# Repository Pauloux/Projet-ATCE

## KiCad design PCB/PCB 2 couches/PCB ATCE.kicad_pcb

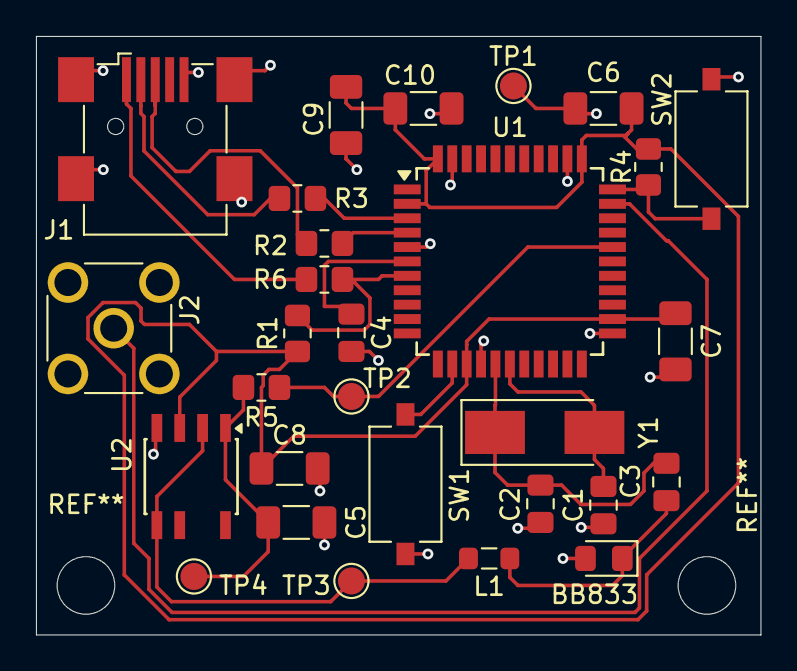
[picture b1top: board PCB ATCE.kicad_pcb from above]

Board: 2 copper layers, 40.2 x 33.2 mm, 29 parts (0 on the bottom side), 18 nets.

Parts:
BB833: D_0805_2012Metric_Pad1.15x1.40mm_HandSolder
C1: 15p; C_0805_2012Metric_Pad1.18x1.45mm_HandSolder
C2: 10p; C_0805_2012Metric_Pad1.18x1.45mm_HandSolder
C3, C4: 1u; C_0805_2012Metric_Pad1.18x1.45mm_HandSolder
C5, C6, C7, C8, C9, C10: 10u; C_1206_3216Metric_Pad1.33x1.80mm_HandSolder
J1: USB_OTG; USB_Mini-B_Wuerth_65100516121_Horizontal
J2: Conn_Coaxial; SMA_Molex_73251-2200_Horizontal
L1: 10u; L_0805_2012Metric_Pad1.05x1.20mm_HandSolder
R1, R6: 0; R_0805_2012Metric_Pad1.20x1.40mm_HandSolder
R2, R3: 22; R_0805_2012Metric_Pad1.20x1.40mm_HandSolder
R4, R5: 5k; R_0805_2012Metric_Pad1.20x1.40mm_HandSolder
SW1, SW2: SW_Push; SW_Tactile_SPST_NO_Straight_CK_PTS636Sx25SMTRLFS
TP1, TP2, TP3, TP4: TestPoint; TestPoint_Pad_D1.5mm
U1: TQFP-44_10x10mm_P0.8mm
U2: SOIC-8-N7_3.9x4.9mm_P1.27mm
Y1: 16MHz; Crystal_SMD_Abracon_ABM3-2Pin_5.0x3.2mm_HandSoldering

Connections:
+5V: C6.1, C7.1, C8.1, C9.1, C10.1, R1.1, R4.1, U1.2 (UVCC), U1.14 (VCC), U1.24 (AVCC), U1.34 (VCC), U1.44 (AVCC), U2.3 (V+)
/D1+: R2.2, U1.4 (D+)
/D1-: R3.2, U1.3 (D-)
/D+: J1.3 (D+), R2.1
/D-: J1.2 (D-), R3.1
GND: BB833.2 (A), C1.1, C2.1, C4.2, C5.2, C6.2, C7.2, C8.2, C9.2, C10.2, J1.5 (GND), J1.6 (Shield), J2.2 (Ext), SW1.1, SW2.2, TP1.1, U1.5 (UGND), U1.15 (GND), U1.23 (GND), U1.35 (GND), U1.43 (GND), U2.4 (V-)
unnamed: BB833.1 (K), C3.2, L1.1
unnamed: J1.1 (VBUS), R6.1
unnamed: J2.1 (In), U1.32 ((ICP3/CLK0/OC4A)PC7)
unnamed: R5.1, TP2.1, U1.29 ((ADC12/OC1A/~OC4B/PCINT5)PB5)
unnamed: R4.2, SW2.1, U1.33 ((~HWB)PE2)
unnamed: C4.1, U1.6 (UCAP)
unnamed: R1.2, R6.2, U1.7 (VBUS)
unnamed: C1.2, U1.17 (XTAL1), Y1.2
unnamed: C2.2, C3.1, U1.16 (XTAL2), Y1.1
unnamed: SW1.2, U1.13 (~RESET)
unnamed: C5.1, R5.2, TP4.1, U2.1 (+)
unnamed: L1.2, TP3.1, U2.2 (-), U2.5

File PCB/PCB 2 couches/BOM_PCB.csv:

"Reference","Value","Datasheet","Footprint","Qty","Prix/U"
"BB833","~","https://www.farnell.com/datasheets/1835977.pdf","Diode_SMD:D_0805_2012Metric_Pad1.15x1.40mm_HandSolder","1","0,172 €"
"C1","15p","https://www.yageo.com/en/Chart/Download/pdf/AC0805JRNPO9BN150","Capacitor_SMD:C_0805_2012Metric_Pad1.18x1.45mm_HandSolder","1","0,0742 €"
"C2","10p","https://www.yageo.com/en/Chart/Download/pdf/AC0805JRNPO0BN100","Capacitor_SMD:C_0805_2012Metric_Pad1.18x1.45mm_HandSolder","1","0,067 €"
"C3","1u","https://4donline.ihs.com/images/VipMasterIC/IC/YAGO/YAGO-S-A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","Capacitor_SMD:C_0805_2012Metric_Pad1.18x1.45mm_HandSolder","1","0,0982 €"
"C4","1u","https://4donline.ihs.com/images/VipMasterIC/IC/YAGO/YAGO-S-A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","Capacitor_SMD:C_0805_2012Metric_Pad1.18x1.45mm_HandSolder","1","0,0982 €"
"C5","10u","https://search.kemet.com/component-documentation/download/sp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","Capacitor_SMD:C_1206_3216Metric_Pad1.33x1.80mm_HandSolder","1","1,230 €"
"C6","10u","https://search.kemet.com/component-documentation/download/sp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","Capacitor_SMD:C_1206_3216Metric_Pad1.33x1.80mm_HandSolder","1","1,230 €"
"C7","10u","https://search.kemet.com/component-documentation/download/sp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","Capacitor_SMD:C_1206_3216Metric_Pad1.33x1.80mm_HandSolder","1","1,230 €"
"C8","10u","https://search.kemet.com/component-documentation/download/sp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","Capacitor_SMD:C_1206_3216Metric_Pad1.33x1.80mm_HandSolder","1","1,230 €"
"C9","10u","https://search.kemet.com/component-documentation/download/sp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","Capacitor_SMD:C_1206_3216Metric_Pad1.33x1.80mm_HandSolder","1","1,230 €"
"C10","10u","https://search.kemet.com/component-documentation/download/sp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","Capacitor_SMD:C_1206_3216Metric_Pad1.33x1.80mm_HandSolder","1","1,230 €"
"J1","USB_OTG","https://www.farnell.com/datasheets/2697485.pdf","Connector_USB:USB_Mini-B_Wuerth_65100516121_Horizontal","1","1,000 €"
"J2","Conn_Coaxial","https://4donline.ihs.com/images/VipMasterIC/IC/AMPH/AMPHS064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","Connector_Coaxial:SMA_Molex_73251-2200_Horizontal","1","6,940 €"
"L1","10u","http://www.farnell.com/datasheets/3006832.pdf","Inductor_SMD:L_0805_2012Metric_Pad1.05x1.20mm_HandSolder","1","0,214 €"
"R1","0","https://4donline.ihs.com/images/VipMasterIC/IC/SCMP/SCMPS001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","Resistor_SMD:R_0805_2012Metric_Pad1.20x1.40mm_HandSolder","1","0,015 €"
"R2","22","https://www.yageo.com/upload/media/product/app/datasheet/rch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","Resistor_SMD:R_0805_2012Metric_Pad1.20x1.40mm_HandSolder","1","0,016 €"
"R3","22","https://www.yageo.com/upload/media/product/app/datasheet/rch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","Resistor_SMD:R_0805_2012Metric_Pad1.20x1.40mm_HandSolder","1","0,016 €"
"R4","5k","https://www.farnell.com/datasheets/3937397.pdf","Resistor_SMD:R_0805_2012Metric_Pad1.20x1.40mm_HandSolder","1","0,015 €"
"R5","5k","https://www.farnell.com/datasheets/3937397.pdf","Resistor_SMD:R_0805_2012Metric_Pad1.20x1.40mm_HandSolder","1","0,015€"
"SW1","SW_Push","https://www.farnell.com/datasheets/3148632.pdf","Button_Switch_SMD:SW_Tactile_SPST_NO_Straight_CK_PTS636Sx25SMTRLFS","1","0,937 €"
"SW2","SW_Push","https://www.farnell.com/datasheets/3148632.pdf","Button_Switch_SMD:SW_Tactile_SPST_NO_Straight_CK_PTS636Sx25SMTRLFS","1","0,937 €"
"TP1","TestPoint","~","TestPoint:TestPoint_Keystone_5000-5004_Miniature","1",""
"TP2","TestPoint","~","TestPoint:TestPoint_Keystone_5000-5004_Miniature","1",""
"TP3","TestPoint","~","TestPoint:TestPoint_Keystone_5000-5004_Miniature","1",""
"TP4","TestPoint","~","TestPoint:TestPoint_Keystone_5000-5004_Miniature","1",""
"U1","~","https://ww1.microchip.com/downloads/en/DeviceDoc/Atmel-7766-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","Package_QFP:TQFP-44_10x10mm_P0.8mm","1","5,250 €"
"U2","","https://www.farnell.com/datasheets/630314.pdf","Package_SO:SOIC-8-N7_3.9x4.9mm_P1.27mm","1","0,353 €"
"Y1","16MHz","https://www.farnell.com/datasheets/3153929.pdf","Crystal:Crystal_SMD_Abracon_ABM3-2Pin_5.0x3.2mm_HandSoldering","1","0,258 €"

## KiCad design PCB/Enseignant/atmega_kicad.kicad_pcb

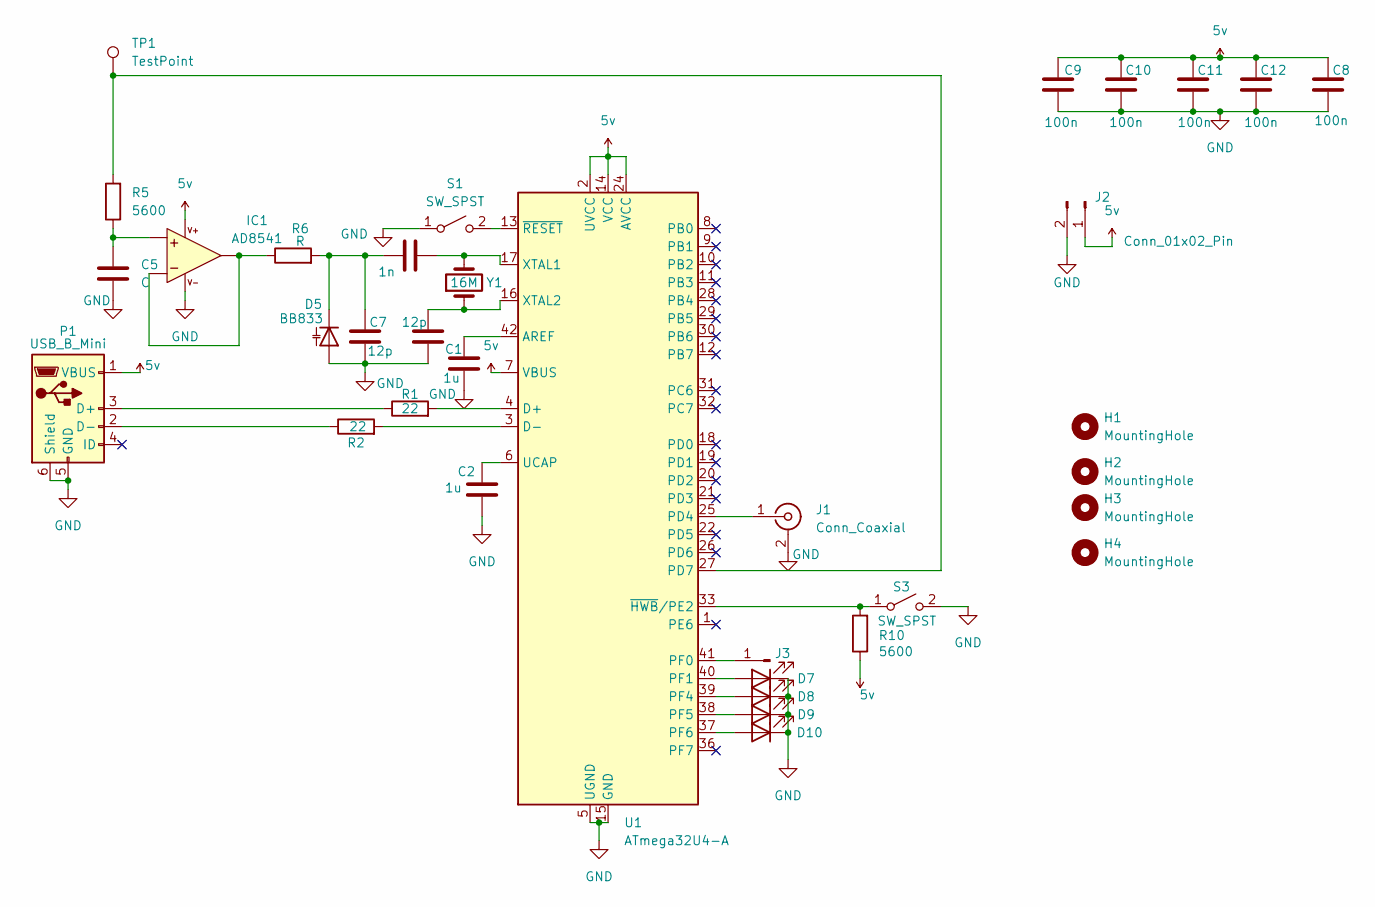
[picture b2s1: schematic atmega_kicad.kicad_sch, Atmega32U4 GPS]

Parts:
C1, C2: 1u; C_0805_2012Metric_Pad1.18x1.45mm_HandSolder
C3: 1n; C_0805_2012Metric_Pad1.18x1.45mm_HandSolder
C4, C7: 12p; C_0805_2012Metric_Pad1.18x1.45mm_HandSolder
C5: C; C_0805_2012Metric_Pad1.18x1.45mm_HandSolder
C8, C9, C10, C11, C12: 100n; C_0805_2012Metric_Pad1.18x1.45mm_HandSolder
D5: BB833; C_0805_2012Metric_Pad1.18x1.45mm_HandSolder
D7, D8, D9, D10: LED; LED_1206_3216Metric_Pad1.42x1.75mm_HandSolder
H1, H2, H3, H4: MountingHole; MountingHole_3mm
IC1: AD8541; SOT-353_SC-70-5; Farnell 1333254
J1: Conn_Coaxial; SMA_Amphenol_132134_Vertical
J2: Conn_01x02_Pin; PinHeader_1x02_P2.54mm_Vertical
J3: Conn_01x01_Pin; PinHeader_1x01_P2.54mm_Vertical
P1: USB_B_Mini; USB_Mini-B_Lumberg_2486_01_Horizontal
R1, R2: 22; R_0805_2012Metric_Pad1.20x1.40mm_HandSolder
R5, R10: 5600; R_0805_2012Metric_Pad1.20x1.40mm_HandSolder
R6: R; R_0805_2012Metric_Pad1.20x1.40mm_HandSolder
S1, S3: SW_SPST; SW_Tactile_SPST_Angled_PTS645Vx39-2LFS
TP1: TestPoint; TestPoint_Pad_1.0x1.0mm
U1: ATmega32U4-A; TQFP-44_10x10mm_P0.8mm
Y1: 16M; Crystal_HC49-U_Vertical

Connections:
5v: C8.2, C9.2, C10.2, C11.2, C12.2, IC1.5 (V+), J2.1, P1.1 (VBUS), R10.1, U1.2 (UVCC), U1.7 (VBUS), U1.14 (VCC), U1.24 (AVCC), U1.34 (VCC), U1.44 (AVCC)
GND: C1.2, C2.2, C4.1, C5.1, C7.2, C8.1, C9.1, C10.1, C11.1, C12.1, D5.2 (A), D7.1 (K), D8.1 (K), D9.1 (K), D10.1 (K), IC1.2 (V-), J1.2 (Ext), J2.2, P1.5 (GND), P1.6 (Shield), S1.1 (A), S3.2 (B), U1.5 (UGND), U1.15 (GND), U1.23 (GND), U1.35 (GND), U1.43 (GND)
unnamed: C3.1, C7.1, D5.1 (K), R6.2
unnamed: D7.2 (A), U1.40 (PF1)
unnamed: D8.2 (A), U1.39 (PF4)
unnamed: D9.2 (A), U1.38 (PF5)
unnamed: D10.2 (A), U1.37 (PF6)
unnamed: C5.2, IC1.3 (+), R5.1
unnamed: IC1.1 (OUT), IC1.4 (-), R6.1
unnamed: J1.1 (In), U1.25 (PD4)
unnamed: J3.1, U1.41 (PF0)
unnamed: P1.3 (D+), R1.1
unnamed: P1.2 (D-), R2.1
unnamed: S1.2 (B), U1.13 (~RESET)
unnamed: R10.2, S3.1 (A), U1.33 (~HWB/PE2)
unnamed: C1.1, U1.42 (AREF)
unnamed: R1.2, U1.4 (D+)
unnamed: R2.2, U1.3 (D-)
unnamed: R5.2, TP1.1, U1.27 (PD7)
unnamed: C2.1, U1.6 (UCAP)
unnamed: C3.2, U1.17 (XTAL1), Y1.2
unnamed: C4.2, U1.16 (XTAL2), Y1.1

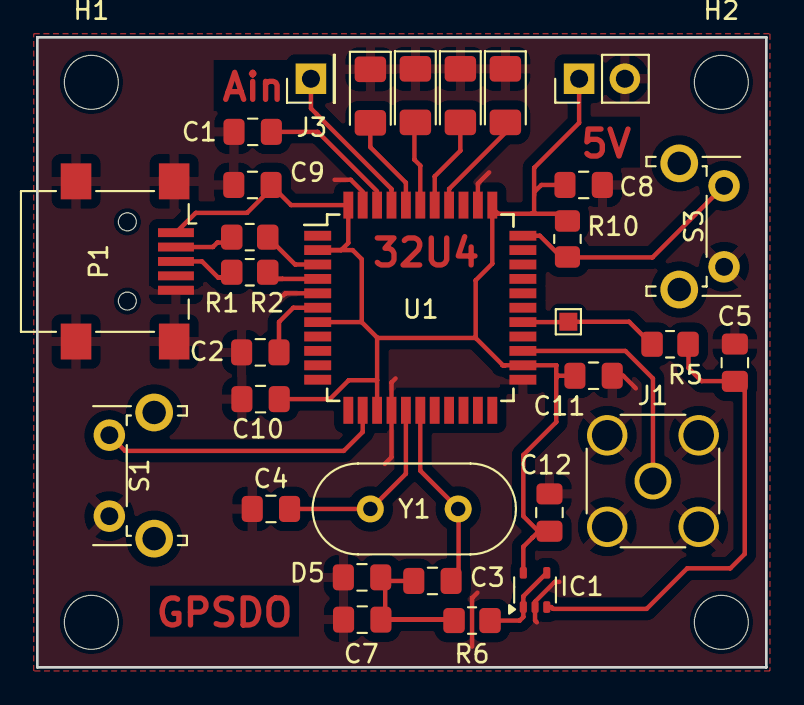
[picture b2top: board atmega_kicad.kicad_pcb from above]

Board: 2 copper layers, 40.5 x 35.0 mm, 35 parts (0 on the bottom side), 22 nets.

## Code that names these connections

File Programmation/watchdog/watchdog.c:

#define F_CPU 16000000UL
#include <avr/io.h>
#include <avr/wdt.h>     // Pour le watchdog
#include <util/delay.h>  // Pour _delay_ms()
#include <avr/interrupt.h>
#include "VirtualSerial.h"

extern USB_ClassInfo_CDC_Device_t VirtualSerial_CDC_Interface;
extern FILE USBSerialStream;

int main(void)
{
    MCUCR |= (1<<JTD);
    MCUCR |= (1<<JTD);
    SetupHardware();
    CDC_Device_CreateStream(&VirtualSerial_CDC_Interface, &USBSerialStream);
    GlobalInterruptEnable();
    DDRF |= (1 << PF1) | (1 << PF4) | (1 << PF5) | (1 << PF6) ;
    PORTF |= (1 << PF1);    
    PORTF &= ~(1 << PF4);   
    PORTF &= ~(1 << PF5);
    PORTF &= ~(1 << PF6);

    _delay_ms(1000); 
    wdt_enable(WDTO_120MS);  
    
    for (uint8_t i = 0; i < 100; i++)
            {
                PORTF ^= (1 << PF4);   
                _delay_ms(100);
                wdt_reset();    
            }
    while (1)
    {
        CDC_Device_ReceiveByte(&VirtualSerial_CDC_Interface);
	CDC_Device_USBTask(&VirtualSerial_CDC_Interface);
	USB_USBTask();
    }

    return 0;
}

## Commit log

2025-02-01 Création du dépôt
2025-02-01 Retrait des fichiers auxilaires de compilation LaTeX et ajout de ces fichiers dans la liste des fichiers ignorés
2025-02-03 Ajout du schéma de la carte OLIMEXINO-32U4
2025-02-03 Ajout du symbole du microcontrôleur ATmega32U4-AU pour KiCAD
2025-02-04 Ajout de la version 0.1 du schéma de Paul + Modification du .gitignore pour ne garder que les fichiers essentiels
2025-02-04 cablage maxime
2025-02-05 correction des erreurs electriques
2025-02-05 Ajout du schéma de Paul au format PDF
2025-02-07 exemple
2025-02-07 suppression test
2025-02-13 Renommage du projet KiCAD de Paul pour qu'il devienne le projet global + Complétion du schéma (quelques points de doute)
2025-02-14 Modification des condensateurs de pieds du résonateur et retrait du point de test de l'alimentation
2025-02-15 Ajout de la justification des choix pour le schéma du PCB
2025-02-15 ajout des empreintes et BOM
2025-02-15 ajout des datasheet pour chaque composant du PCB
2025-02-16 j'ai enlever les 90 degres
2025-02-16 deplace port usb
2025-02-16 PCB : retouche port usb et coax
2025-02-17 suppression dossier Maxime + Deplacement des trou pcb
2025-02-26 pcb 1 couche
2025-02-28 Simplification du .gitignore pour que tous les fichiers inutiles des PCB soient ignorés
2025-02-28 Ajout des fichiers .kicad_prl à la liste des fichiers ignorés
2025-03-01 Modification du routage des paires différentielles de l'USB pour le PCB 2 couches
2025-03-01 Ajout d'un fichier (je ne sais pas trop à quoi il sert)
2025-03-01 Création d'un projet KiCAD dédié à la simulation
2025-03-01 Suppression de PCB ATCE
2025-03-15 Ajout des diaporamas de présentation
2025-03-15 Réalisation de la simulation approximative de l'oscillateur
2025-03-15 Passage des fichiers KiCAD à la version 9
2025-03-16 Changement des ports pour le PWM et l'ICP
2025-03-16 Création du compte rendu et rédaction au brouillon de la réalisation du schéma
2025-03-16 modification pcb une couche suite au changement du pwm
2025-03-17 modification pcb (empreinte test point + routage nouveau pwm)
2025-03-17 Ajout de datasheets
2025-03-19 pcb modif
2025-03-19 Simulation
2025-03-19 Prix PCB 2 couches
2025-03-19 Prix du PCB
2025-04-07 Ajout de la présentation du début de la semaine de projet
2025-04-07 Ajout du PCB fourni par les enseignants
2025-04-07 Changements des fichiers pour la simulation (je ne sais plus ce qu'on a fait)
2025-04-07 Ajout de Blink
2025-04-07 Correction du programme Blink en Hello_world
2025-04-07 Ajout du code pour utiliser le PWM sur 8 bits
2025-04-07 Ajout du code pour utiliser le PWM sur 10 bits
2025-04-07 Ajout de délais pour un duty_cycle de 0 et 100% (à vérifier à l'oscilloscope)
2025-04-08 Ajout de la bibliothèque LUFA
2025-04-08 bibliographie
2025-04-08 Ajout du programme qui permet de mesurer la fréquence de l'oscillateur à partir du 1PPS
2025-04-08 Ajout de la gestion de l'USB et retrait du délai dans le programme de test de l'ICP
2025-04-08 Ajout des programmes pour tracer l'évolution de la fréquence en fonction du temps (ICP)
2025-04-08 Ajout du programme pour voir l'influence de la tension de polarisation de la Varicap sur la fréquence + graphique
2025-04-08 Ajout des légendes des axes pour les graphes
2025-04-08 Ajout des mesures de la fréquence en faisant varier la température du quartz
2025-04-08 Modification du programme qui mesure l'influence de la Varicap afin que le duty cycle aille de 0 à 100% + Mesure
2025-04-09 boite 3D
2025-04-09 modification fichier 3D
2025-04-09 photos soudures PCB
2025-04-09 Ajout du programme qui permet de tracer la réponse indicielle du système
2025-04-09 Ajout du watchdog pour la fin
2025-04-09 Réalisation du programme qui permet de réaliser un régulateur PI pour réguler la fréquence du quartz
2025-04-09 Mise au propre du fichier permettant de tester le watchdog
2025-04-10 Correction boite 3D
2025-04-10 suprresion backup
2025-04-11 Ajout d'un délai avant d'envoyer les mesures via USB
2025-04-11 Ajout du script MATLAB qui permet de comparer les performances avec et sans régulation
2025-04-11 Ajout du chien de garde dans l'asservissement PI et de commentaires
2025-04-11 Ajout des valeurs relevées pendant la vidéo
2025-04-12 Modification de l'asservissement pour ne plus compter le nombre de cycles ICP réalisés
2025-04-12 Ajout d'une mesure sur une longue durée
2025-04-12 Ajout de la section pour les annexes et utilisation de la commande faite pour la bibliographie
2025-04-12 Modification du style des liens et des entêtes de page
2025-04-12 Rédaction de l'introduction
2025-04-12 choix des composants
2025-04-12 selection des composants
2025-04-12 ajuster la BOM
2025-04-13 redaction partie routage PCB
2025-04-13 Modification de la partie 'Schéma électrique' dans le compte rendu
2025-04-13 Mise au propre du schéma électrique
2025-04-13 simulation AC
2025-04-13 Ajout de la simulation RC et Estimation Prix
2025-04-13 Correction des avertissements de compilation
2025-04-13 Ajout des images CR
2025-04-13 Rangement des images (ressources)
2025-04-13 Rédaction du transfert du programme
2025-04-13 Modification des commentaires dans le programme du PWM
2025-04-13 Rédaction de la programmation du PWM
2025-04-13 modification des dispositions
2025-04-13 Rédaction de la programmation de l'ICP
2025-04-13 redaction partie soudures des composants
2025-04-13 Rédaction de la programmation de l'asservissement
2025-04-13 redaction boitier 3D
2025-04-14 Rédaction de la programmation du watchdog
2025-04-14 Rédaction de la conclusion
2025-04-14 Ajout du compte rendu au format pdf
2025-04-14 Correction des fautes de français
2025-04-14 Ajout du lien vers le dépôt Github
2025-04-14 Relecture
2025-04-14 modifications erreurs : choix composants
2025-04-14 Ajout du bon tableau RC et Calcul theorique de Tau
2025-04-14 modif des fichiers 3D + assemblage
2025-04-14 prise des captures d'ecrans
2025-04-14 ajout des figures en annexe +relecture
2025-04-14 ajout d'un lien de telechargement
2025-04-14 Ajout du lien vers la vidéo de démonstration dans le compte rendu
2025-04-14 Mise en page
2026-03-30 Add LICENSE
